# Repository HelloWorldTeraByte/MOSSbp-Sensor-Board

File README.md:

# MOSSbp-Sensor-Board
MOSSbp(Multi-material Open Source Secure Bio Printer) is an IoT connected bio printer. Sensor board including pressure, humidty, temperature, VCO, UV/IR and CO2.

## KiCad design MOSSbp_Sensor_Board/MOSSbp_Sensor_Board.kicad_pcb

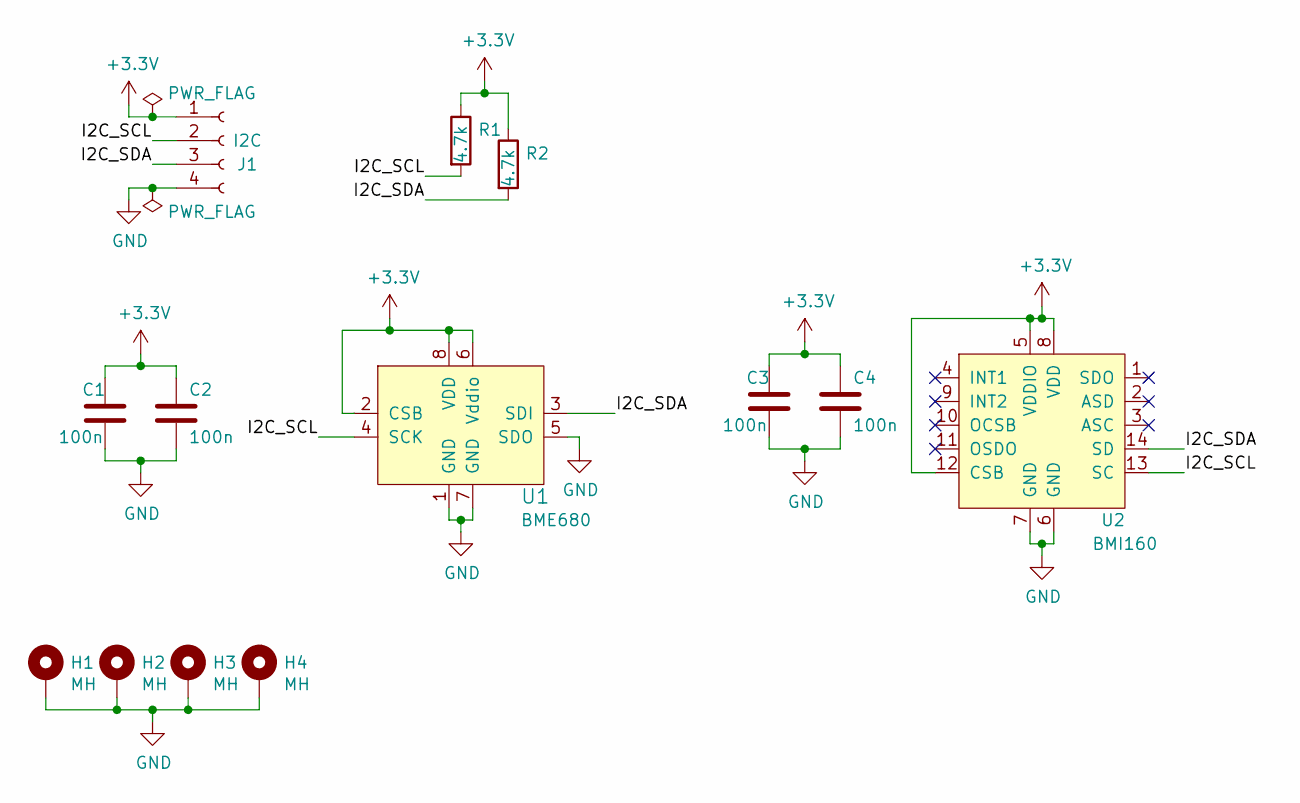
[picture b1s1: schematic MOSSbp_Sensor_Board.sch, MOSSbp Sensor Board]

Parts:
C1, C2, C3, C4: 100n; C_0603_1608Metric_Pad1.05x0.95mm_HandSolder; Digi-Key_PN 311-1341-1-ND
H1, H2, H3, H4: MH; MountingHole_2.2mm_M2_ISO14580_Pad
J1: I2C; JST_GH_SM04B-GHS-TB_1x04-1MP_P1.25mm_Horizontal; Digi-Key_PN 455-1566-1-ND
R1, R2: 4.7k; R_0603_1608Metric_Pad1.05x0.95mm_HandSolder; Digi-Key_PN 311-4.7KGRCT-ND
U1: BME680; MPN BME680; Digi-Key_PN 828-1077-1-ND
U2: BMI160; MPN BMI160; Digi-Key_PN 828-1057-1-ND

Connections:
+3V3: C1.1, C2.1, C3.1, C4.1, J1.1, R1.1, R2.1, U1.2 (CSB), U1.6 (Vddio), U1.8 (VDD), U2.5 (VDDIO), U2.8 (VDD), U2.12 (CSB)
/I2C_SCL: J1.2, R1.2, U1.4 (SCK), U2.13 (SC)
/I2C_SDA: J1.3, R2.2, U1.3 (SDI), U2.14 (SD)
GND: C1.2, C2.2, C3.2, C4.2, H1.1, H2.1, H3.1, H4.1, J1.4, U1.1 (GND), U1.5 (SDO), U1.7 (GND), U2.6 (GND), U2.7 (GND)

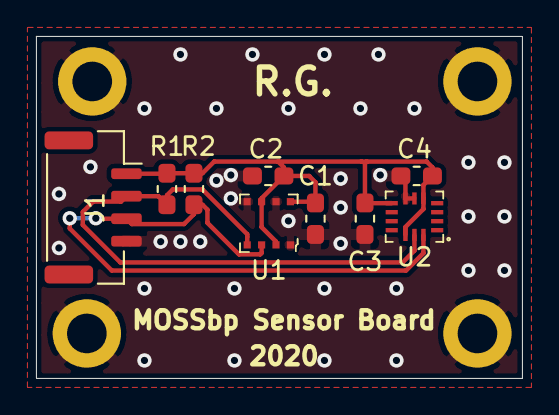
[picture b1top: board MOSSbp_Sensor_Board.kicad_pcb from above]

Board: 2 copper layers, 27.0 x 19.0 mm, 13 parts (0 on the bottom side), 4 nets.

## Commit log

2020-01-24 Initial commit of PCB files
2020-01-24 Added BME680 and I2C
2020-01-27 Finished PCB board
